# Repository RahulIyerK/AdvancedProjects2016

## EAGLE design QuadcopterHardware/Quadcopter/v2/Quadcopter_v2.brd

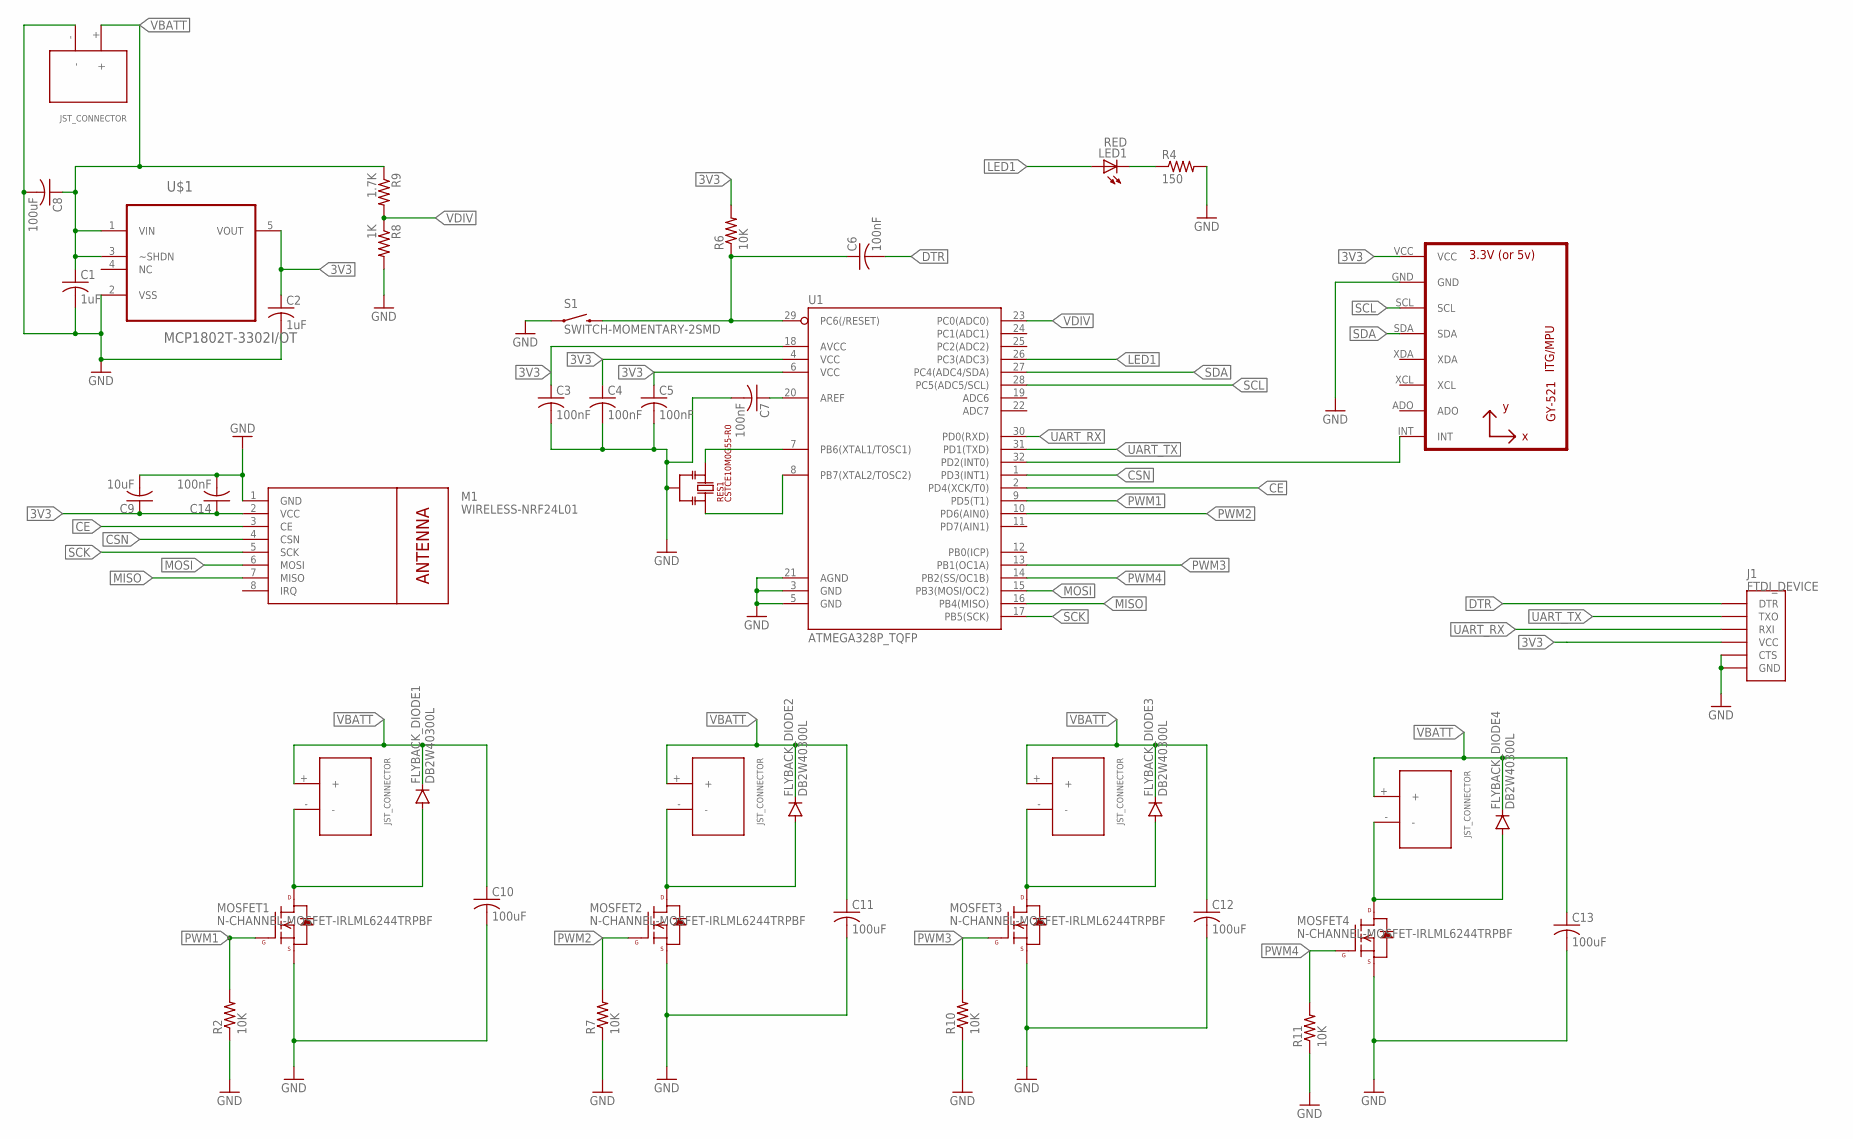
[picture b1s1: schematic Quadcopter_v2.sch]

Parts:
C1, C2: 1uF; C0603
C3, C4, C5, C6, C7, C14: 100nF; C0603
C8, C10, C11, C12, C13: 100uF; C1210
C9: 10uF; C0603
FLYBACK_DIODE1, FLYBACK_DIODE2, FLYBACK_DIODE3, FLYBACK_DIODE4: DB2W40300L; MINI2-F3-B
J1: FTDI_DEVICE; FTDI_DEVICE_SIDE
LED1: RED; CHIP-LED0603
M1: WIRELESS-NRF24L01
MOSFET1, MOSFET2, MOSFET3, MOSFET4: N-CHANNEL-MOSFET-IRLML6244TRPBF; SOT23-3
MOTOR, MOTOR1, MOTOR2, MOTOR3: JST_CONNECTOR_FEMALE
R2, R6, R7, R10, R11: 10K; R0603
R4: 150; R0603
R8: 1K; R0603
R9: 1.7K; R0603
RES1: CSTCE10M0G55-R0; CSTCE16M0V53-R0
S1: SWITCH-MOMENTARY-2SMD; TACTILE-SWITCH-SMD
U1: ATMEGA328P_TQFP; TQFP32-08
U3: GY-521MPU6050; GY-521
U$1: MCP1802T-3302I/OT; SOT95P270X145-5N
U$2: JST_Battery; JST_CONNECTOR_FEMALE

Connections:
3V3: C2.1, C3.1, C4.1, C5.1, C9.1, C14.1, J1.P$4 (VCC), M1.2 (VCC), R6.2, U1.4 (VCC), U1.6 (VCC), U1.18 (AVCC), U3.VCC, U$1.5 (VOUT)
ACC_INT: U1.32 (PD2(INT0)), U3.INT
AREF: C7.1, U1.20 (AREF)
CE: M1.3 (CE), U1.2 (PD4(XCK/T0))
CSN: M1.4 (CSN), U1.1 (PD3(INT1))
DRAIN1: FLYBACK_DIODE1.POS (PPIN), MOSFET1.3 (D), MOTOR.-
DRAIN2: FLYBACK_DIODE2.POS (PPIN), MOSFET2.3 (D), MOTOR1.-
DRAIN3: FLYBACK_DIODE3.POS (PPIN), MOSFET3.3 (D), MOTOR2.-
DRAIN4: FLYBACK_DIODE4.POS (PPIN), MOSFET4.3 (D), MOTOR3.-
DTR: C6.2, J1.P$1 (DTR)
GND: C1.2, C2.2, C3.2, C4.2, C5.2, C7.2, C8.2, C9.2, C10.2, C11.2, C12.2, C13.2, C14.2, J1.P$5 (CTS), J1.P$6 (GND), M1.1 (GND), MOSFET1.2 (S), MOSFET2.2 (S), MOSFET3.2 (S), MOSFET4.2 (S), R2.1, R4.2, R7.1, R8.2, R10.1, R11.1, RES1.P$2, S1.1, U1.3 (GND), U1.5 (GND), U1.21 (AGND), U3.GND, U$1.2 (VSS), U$2.-
LED1: LED1.A, U1.26 (PC3(ADC3))
LEDRESISTOR: LED1.C, R4.1
MISO: M1.7 (MISO), U1.16 (PB4(MISO))
MOSI: M1.6 (MOSI), U1.15 (PB3(MOSI/OC2))
PWM1: MOSFET1.1 (G), R2.2, U1.9 (PD5(T1))
PWM2: MOSFET2.1 (G), R7.2, U1.10 (PD6(AIN0))
PWM3: MOSFET3.1 (G), R10.2, U1.13 (PB1(OC1A))
PWM4: MOSFET4.1 (G), R11.2, U1.14 (PB2(SS/OC1B))
RST: C6.1, R6.1, S1.3 (2), U1.29 (PC6(/RESET))
SCK: M1.5 (SCK), U1.17 (PB5(SCK))
SCL: U1.28 (PC5(ADC5/SCL)), U3.SCL
SDA: U1.27 (PC4(ADC4/SDA)), U3.SDA
UART_RX: J1.P$3 (RXI), U1.30 (PD0(RXD))
UART_TX: J1.P$2 (TXO), U1.31 (PD1(TXD))
VBATT: C1.1, C8.1, C10.1, C11.1, C12.1, C13.1, FLYBACK_DIODE1.NEG (GPIN), FLYBACK_DIODE2.NEG (GPIN), FLYBACK_DIODE3.NEG (GPIN), FLYBACK_DIODE4.NEG (GPIN), MOTOR.+, MOTOR1.+, MOTOR2.+, MOTOR3.+, R9.1, U$1.1 (VIN), U$1.3 (~SHDN), U$2.+
VDIV: R8.1, R9.2, U1.23 (PC0(ADC0))
XTAL1: RES1.P$3, U1.7 (PB6(XTAL1/TOSC1))
XTAL2: RES1.P$1, U1.8 (PB7(XTAL2/TOSC2))

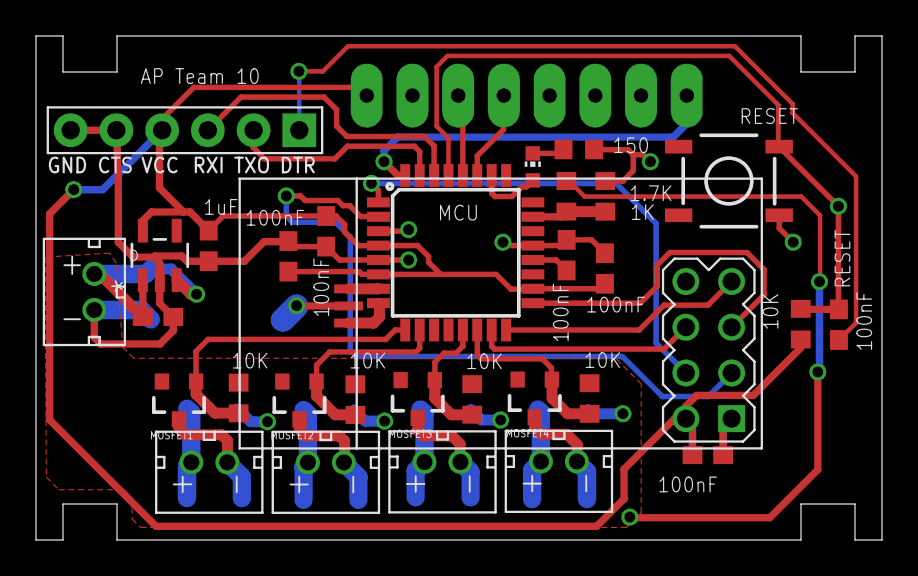
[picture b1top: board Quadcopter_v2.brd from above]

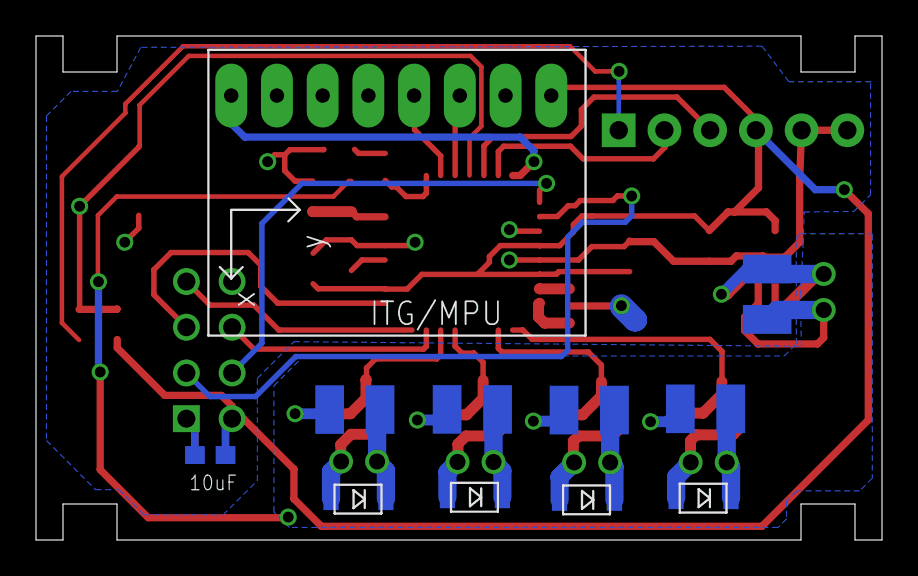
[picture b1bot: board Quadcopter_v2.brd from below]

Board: 2 copper layers, 47.0 x 28.0 mm, 43 parts (11 on the bottom side), 29 nets.

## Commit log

2016-10-11 Initial project commit
2016-10-15 Initial upload for TeensyTranceiver for ButtonLighter
2016-10-15 arduinoslave for buttonlighter project
2016-10-15 Revised TeensyTranciever in ButtonLighter to have appropriate output and to compile properly
2016-10-15 Added updated ButtonLighter code
2016-10-15 fixed errors: pinMode needs to be set as OUTPUT
2016-10-15 fixed errors
2016-10-15 Adjusted lastDebounceTime to be different for each RGY LED in ButtonLighter
2016-10-15 Finalized version of TeensyTranceiver
2016-10-15 fixed error: pins were not set as OUTPUT
2016-10-17 Initial commit for the Space Team Wired project
2016-10-17 The first draft of the TeensyPlayer1 program for Space Team Wired
2016-10-17 The first changes to the TeensyPlayer1 file
2016-10-17 player2side
2016-10-17 made modifications to the SoftwareSerial writing and reading (writes and reads array of characters now, which should work....)
2016-10-18 Removed six character bug.
2016-10-18 more fixes
2016-10-18 array now instead of string
2016-10-19 reduced character array size to 100 from 1000 for game sequence array (1000 unnecessary for the scope of this project...; changed Serial.readBytesUntil() to Serial.readBytes (the newline character ch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
2016-10-25 Initial Commit for Space Team Wireless
2016-10-29 library for RF24 Communication (part of the space team wireless lab) :)
2016-10-30 files for checkpoint 2
2016-11-01 Committing to check
2016-11-01 alskdjgasdg
2016-11-05 sweet hallelujah cullen just owned us...
2016-11-07 finished code
2016-11-07 changed LED pins for Teensy
2016-11-07 Added serial print line
2016-11-07 done with project 4\!
2016-11-11 Initial Commit for Battery Read
2016-11-11 made changes to Battery Voltage Calculation
2016-11-12 Initial Commit with Wireless Button Check
2016-11-12 fixed issues with BatteryRead sketch (Vcc on Pro Mini was 3.496 volts (tested using a multimeter) instead of stated 3.3V)
2016-11-12 Renamed files to more relevant names
2016-11-12 Edited files in WirelessButtonCheck to have a smart lighting system
2016-11-13 Some revisions to TeensyReceiver and ArduinoAirMouse
2016-11-13 done with the lab
2016-11-13 TeensyReceiver final modifications
2016-11-19 The initial commit and draft for the AirMouse project
2016-11-19 updates to teensy code
2016-11-22 asdf
2016-11-22 Added a rough draft for the receiver to move the mouse
2016-11-23 final changes to airmouse...it works\!
2016-11-23 changes to improve program speed and readability
2016-11-23 comments to code
2016-11-23 made code more compact
2017-01-05 cleaned up repo
2017-01-17 Initial commit for QuadcopterHardware
2017-01-19 Added schematic for the motor driver
2017-01-20 Update to MotorDriver schematic
2017-01-20 Updated MotorDriver to Version 3
2017-01-25 The original upload for the quadcopter schematic
2017-01-25 added to schematic...almost done :)
2017-01-29 Version 2.0 of Schematic
2017-02-05 updates to schematic
2017-02-06 more updates
2017-02-08 more updates, generated board
2017-02-09 started working on the board...fixed errors in schematic
2017-02-10 more work on the board
2017-02-10 more work on board
2017-02-11 Made some groups of components
2017-02-13 did some more work on the PCB-added some polygons for GND and VBATT lines
2017-02-13 more work...
2017-02-13 more work
2017-02-13 almost there
2017-02-15 getting there
2017-02-15 draft 1 done, needs checking
2017-02-15 routed unrouted airwires
2017-02-15 ran DRC w/ OSH Park DRU file
2017-03-04 started work on version 2
2017-03-04 v2 updates
2017-03-04 Delete .DS_Store
    deleted unnecessary files
2017-03-04 fixed board text
2017-03-04 removed unnecessary trace
2017-03-05 fixed board text (OSH Park scaling caused unwanted text cropping
2017-03-05 Revisions to version 2
2017-03-05 moved ground pour
2017-03-05 Removed GRN label on connector J7
2017-03-05 Initial commit for version 3
2017-03-06 final fixes
2017-04-11 final (cullen rev)
2017-04-23 Added Arduino file that contains a class for the PID Algorithm
2017-05-07 moved files to a Quadcopter Software folder and added a radio testing file
2017-05-07 removed old file
2017-05-08 updated the radio testing software and added battery read testing software
2017-05-08 added PWM test software
2017-05-08 Fixed a bug in the PIDErrorToCorrection() method
2017-05-09 fixed and added part tests
2017-05-17 started on main quadcopter software
2017-05-17 Updates to the PID Algorithm code
2017-05-17 Added the PID Algorithm to Quadcopter.ino file and made a skeleton for the PWM, receiver, and IMU code
2017-05-17 changed pin definition for radio CE and CSN
2017-05-24 Wrote in code to adjust the motors
2017-06-02 modified software after testing MPU output in the lab...need to test PID next time.

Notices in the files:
parts and their libraries:
SparkFun-Aesthetics: Licensing: Creative Commons ShareAlike 4.0 International - https://creativecommons.org/licenses/by-sa/4.0
